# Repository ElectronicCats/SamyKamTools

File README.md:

# SamyKamTools

SamyKam - A set of pentesting tools to test Mag-Stripe readers and tokenization processes

Code and hardware integration by [Salvador Mendoza] (https://salmg.net)

PCB design and advisory by Team work with [electronicats] (https://twitter.com/electronicats)

Named the tool in honor of Samy Kamkar (http://samy.pl)
For his hard work and community support

## Features
It is a MagSpoof but specfically designed for Raspberry Pi:
- OLED for prepared attacks
- Rotary endoder for navigation menu

Support:
Mini-shell for basic commands implementing Bluetooth and Webserver independently
- change parameters without ssh
- send any shell command using Bluetooth

## Installation 

### Manual

```
apt-get update 
apt-get install python-dev python-setuptools swig python-bluez gcc-avr binutils-avr avr-libc

# gdata-2
curl -L https://pypi.python.org/packages/a8/70/bd554151443fe9e89d9a934a7891aaffc63b9cb5c7d608972919a002c03c/gdata-2.0.18.tar.gz#md5=13b6e6dd8f9e3e9a8e005e05a8329408 | tar xzf -
cd gdata-2.0.18
python setup.py install

# WiringPi
git clone git://git.drogon.net/wiringPi
cd wiringPi
./build

# WiringPi-Python
git clone --recursive https://github.com/ElectronicsCats/WiringPi-Python
cd WiringPi-Python
./build.sh
python setup.py install

# SPIDEV
git clone https://github.com/doceme/py-spidev
cd py-spidev
python setup.py install

# Adafruit_SSD1306
git clone https://github.com/adafruit/Adafruit_Python_SSD1306
cd Adafruit_Python_SSD1306
sudo python setup.py install

# py-gaugette
git clone https://github.com/guyc/py-gaugette
cd py-gaugette
sudo python setup.py install

#Flask
pip install flask

#SamyKamTools
git clone https://github.com/ElectronicsCats/SamyKamTools
cd SamyKamTools
sudo python SamyKam.py
```

### Automatic Experimental

```
curl https://raw.githubusercontent.com/ElectronicsCats/SamyKamTools/master/install.sh | sudo sh
```

## License

The MagSpoofPi code is under Samy Kamkar license terms, for more information visit https://github.com/samyk/magspoof

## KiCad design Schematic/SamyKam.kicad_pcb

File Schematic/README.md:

# SamyKamTools

- KiCad

Electronic Cats invests time and resources providing this open source design, please support Electronic Cats and open-source hardware by purchasing products from Electronic Cats!

Designed by Electronic Cats.

Hardware released under an CERN Open Hardware Licence v1.2. See the LICENSE_HARDWARE file for more information.

Electronic Cats is a registered trademark, please do not use if you sell these PCBs.

16 January 2017

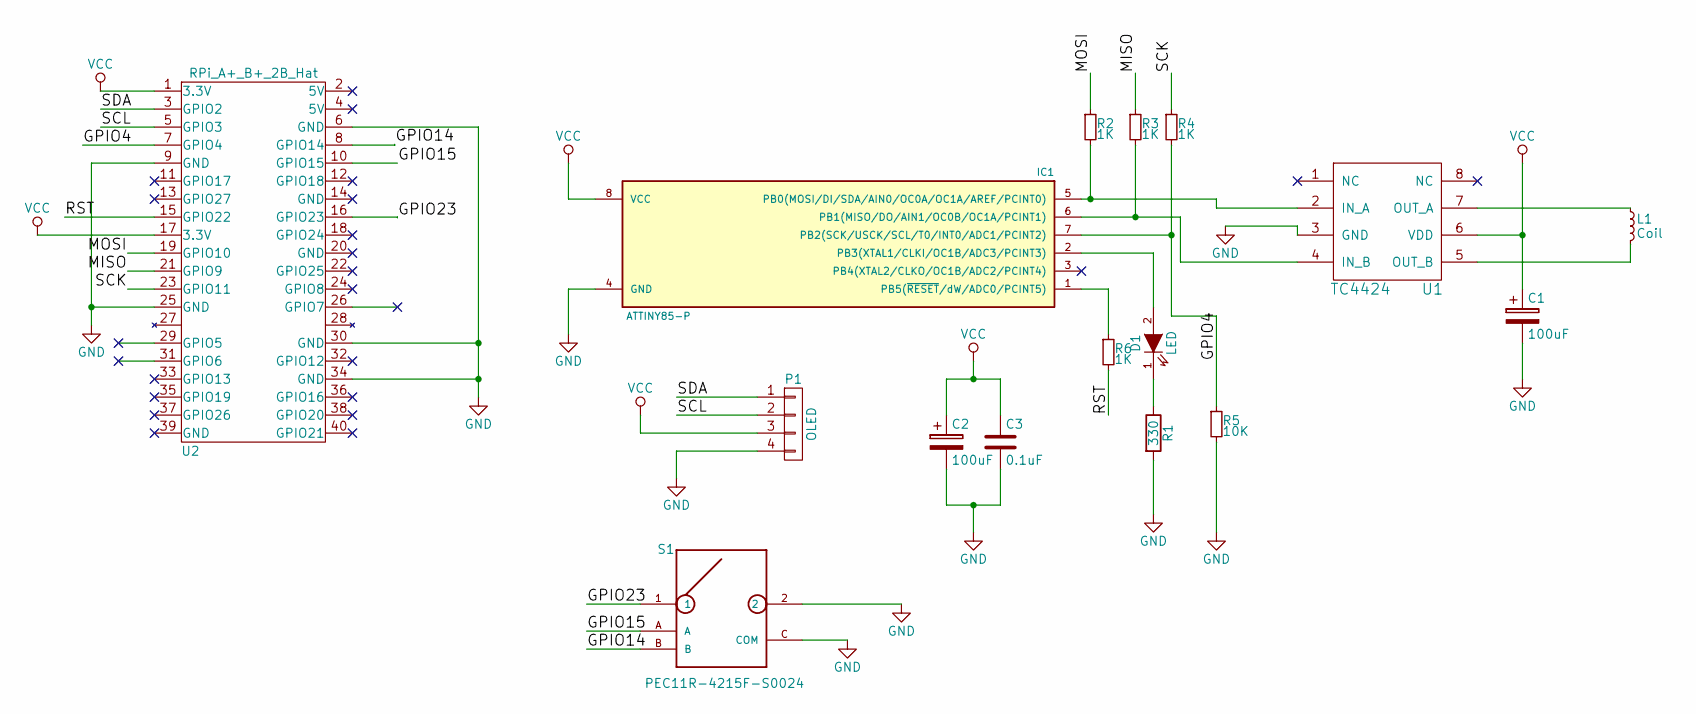
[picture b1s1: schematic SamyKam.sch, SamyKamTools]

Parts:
C1, C2: 100uF; TantalC_SizeA_EIA-3216_HandSoldering
C3: 0.1uF; C_0805_HandSoldering
D1: LED; LED_0805
IC1: ATTINY85-P; SOIC-8-N
L1: Coil; Resistor_Horizontal_RM7mm
P1: OLED; Pin_Header_Straight_1x04
R1: 330; R_0805_HandSoldering
R2, R3, R4, R6: 1K; R_0805_HandSoldering
R5: 10K; R_0805_HandSoldering
S1: PEC11R-4215F-S0024; SW_PEC11R-4215F-S0024
U1: TC4424; SOIC-8-N
U2: RPi_A+_B+_2B_Hat; z_RPiZero_Hat_NPTH

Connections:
/GPIO4: IC1.7 (PB2(SCK/USCK/SCL/T0/INT0/ADC1/PCINT2)), R4.2, R5.1, U2.7 (GPIO4)
/GPIO14: S1.B, U2.8 (GPIO14)
/GPIO15: S1.A, U2.10 (GPIO15)
/GPIO23: S1.1, U2.16 (GPIO23)
/MISO: R3.1, U2.21 (GPIO9)
/MOSI: R2.1, U2.19 (GPIO10)
/RST: R6.2, U2.15 (GPIO22)
/SCK: R4.1, U2.23 (GPIO11)
/SCL: P1.2, U2.5 (GPIO3)
/SDA: P1.1, U2.3 (GPIO2)
GND: C1.2, C2.2, C3.2, IC1.4 (GND), P1.4, R1.2, R5.2, S1.2, S1.C (COM), U1.3 (GND), U2.6 (GND), U2.9 (GND), U2.25 (GND), U2.30 (GND), U2.34 (GND)
unnamed: D1.1 (K), R1.1
unnamed: D1.2 (A), IC1.2 (PB3(XTAL1/CLKI/OC1B/ADC3/PCINT3))
unnamed: IC1.1 (PB5(~RESET~/dW/ADC0/PCINT5)), R6.1
unnamed: IC1.5 (PB0(MOSI/DI/SDA/AIN0/OC0A/OC1A/AREF/PCI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), R2.2, U1.2 (IN_A)
unnamed: IC1.6 (PB1(MISO/DO/AIN1/OC0B/OC1A/PCINT1)), R3.2, U1.4 (IN_B)
unnamed: L1.1, U1.7 (OUT_A)
unnamed: L1.2, U1.5 (OUT_B)
VCC: C1.1, C2.1, C3.1, IC1.8 (VCC), P1.3, U1.6 (VDD), U2.1 (3.3V), U2.17 (3.3V)

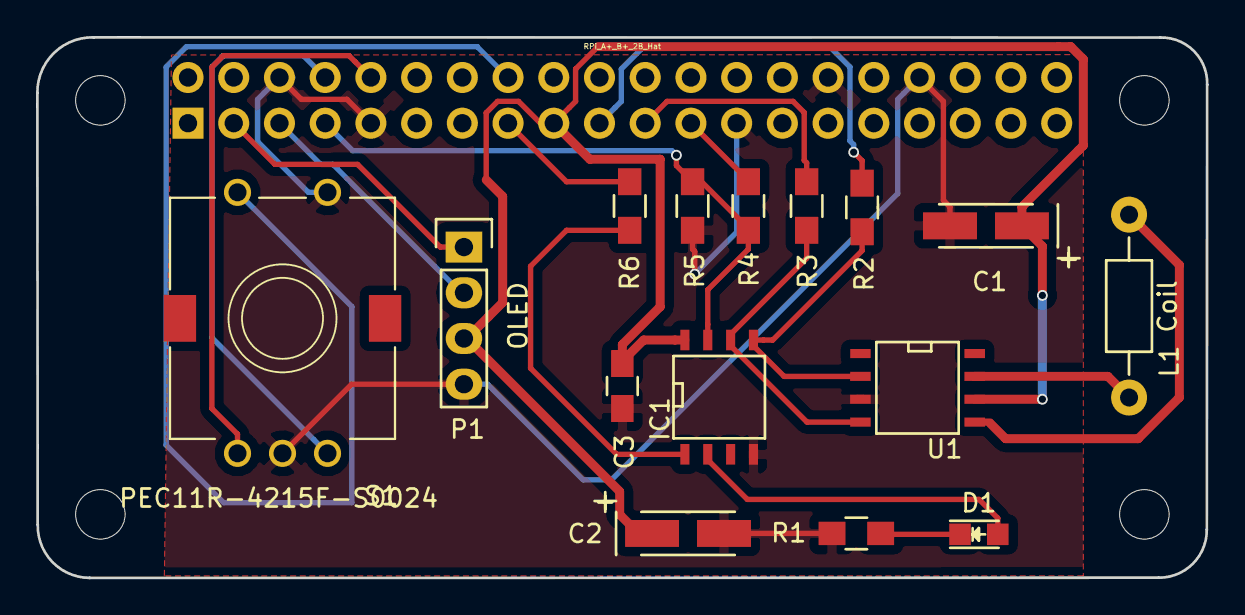
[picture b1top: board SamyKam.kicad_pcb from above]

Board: 2 copper layers, 65.0 x 30.0 mm, 16 parts (0 on the bottom side), 19 nets.

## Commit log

2017-01-16 Create headMagSpoofPI
2017-01-16 Create tailMagSpoofPI
2017-01-16 Add ttf
2017-01-16 beta script install
2017-01-16 Add gitignore
2017-01-16 Add images 3D
2017-01-16 Add files Kicad
2017-01-16 Add README Hardware
2017-02-03 Fix Connection Grounds
2017-02-28 Update SamyKam.py
    Some methods changed in the last version of rotary encoder library
2017-07-22 Create q
